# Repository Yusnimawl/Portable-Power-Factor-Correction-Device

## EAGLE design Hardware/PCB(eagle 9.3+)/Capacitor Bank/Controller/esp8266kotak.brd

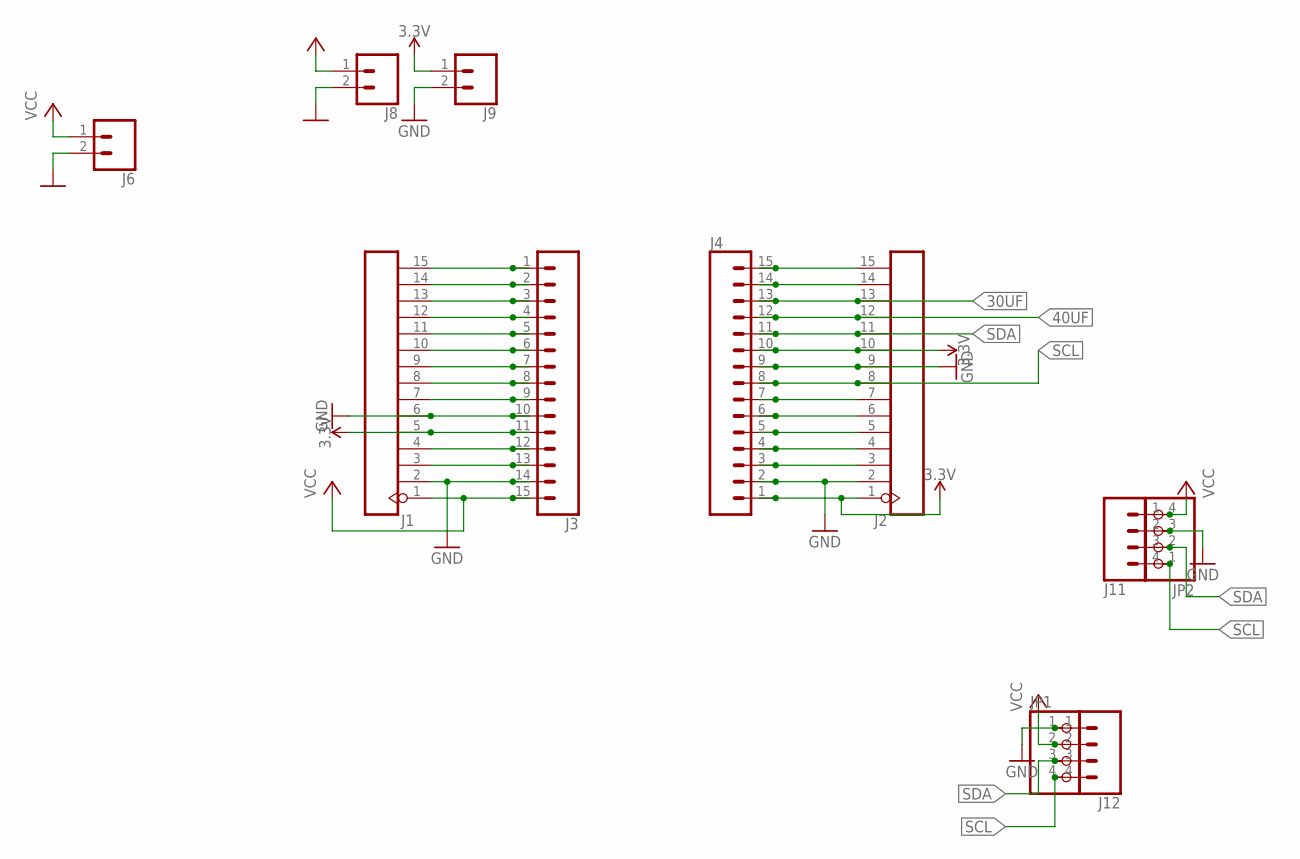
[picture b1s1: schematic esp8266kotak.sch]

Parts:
J1, J2: HEADER-15P2.54; 15P-2.54
J3, J4: CONN_15; 1X15
J6, J8, J9: CONN_02; 1X02
J11, J12: CONN_04; 1X04
JP1, JP2: PINHD-1X4/90; 1X04/90

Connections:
3.3V: J1.5, J2.1, J2.10, J3.11, J4.1, J4.10, J9.1
30UF: J2.13, J4.13
40UF: J2.12, J4.12
GND: J1.2, J1.6, J2.2, J2.9, J3.10, J3.14, J4.2, J4.9, J6.2, J8.2, J9.2, J11.2, J12.1, JP1.1, JP2.3
unnamed: J1.3, J3.13
unnamed: J1.4, J3.12
unnamed: J1.7, J3.9
unnamed: J1.8, J3.8
unnamed: J1.9, J3.7
unnamed: J1.10, J3.6
unnamed: J1.11, J3.5
unnamed: J1.12, J3.4
unnamed: J1.13, J3.3
unnamed: J1.14, J3.2
unnamed: J1.15, J3.1
unnamed: J2.3, J4.3
unnamed: J2.4, J4.4
unnamed: J2.5, J4.5
unnamed: J2.6, J4.6
unnamed: J2.7, J4.7
unnamed: J2.14, J4.14
unnamed: J2.15, J4.15
SCL: J2.8, J4.8, J11.4, J12.4, JP1.4, JP2.1
SDA: J2.11, J4.11, J11.3, J12.3, JP1.3, JP2.2
VCC: J1.1, J3.15, J6.1, J8.1, J11.1, J12.2, JP1.2, JP2.4

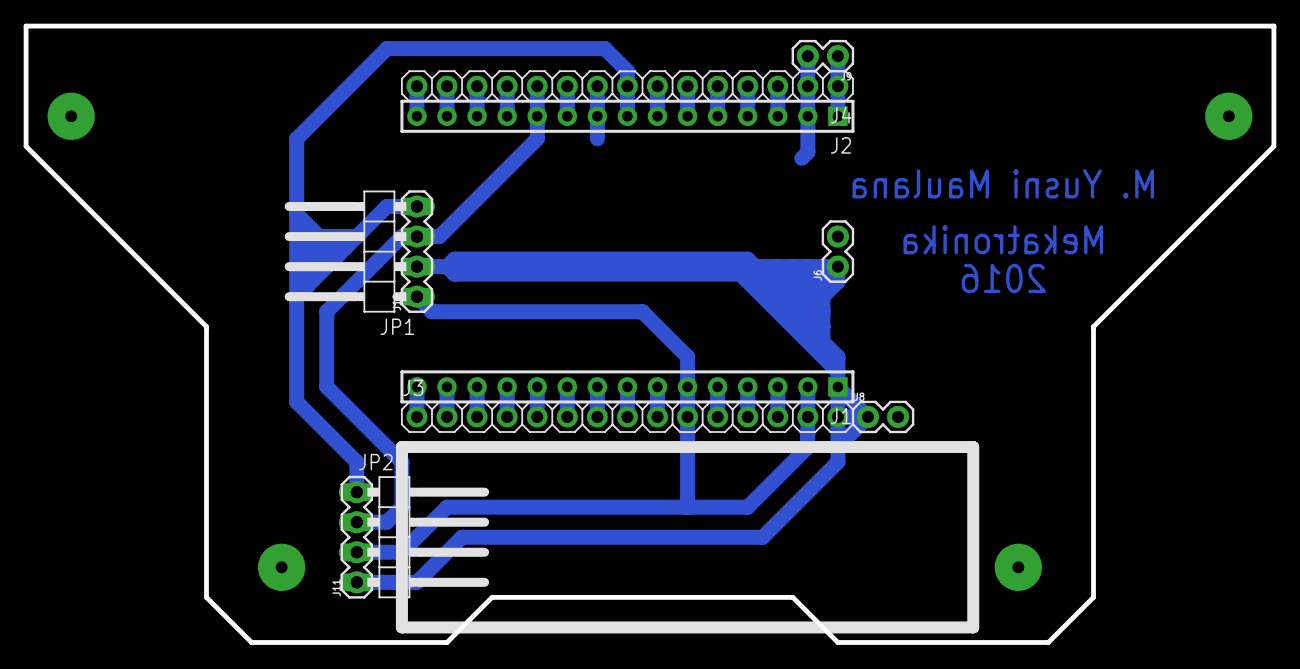
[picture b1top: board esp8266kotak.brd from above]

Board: 2 copper layers, 105.4 x 52.1 mm, 11 parts (0 on the bottom side), 25 nets.

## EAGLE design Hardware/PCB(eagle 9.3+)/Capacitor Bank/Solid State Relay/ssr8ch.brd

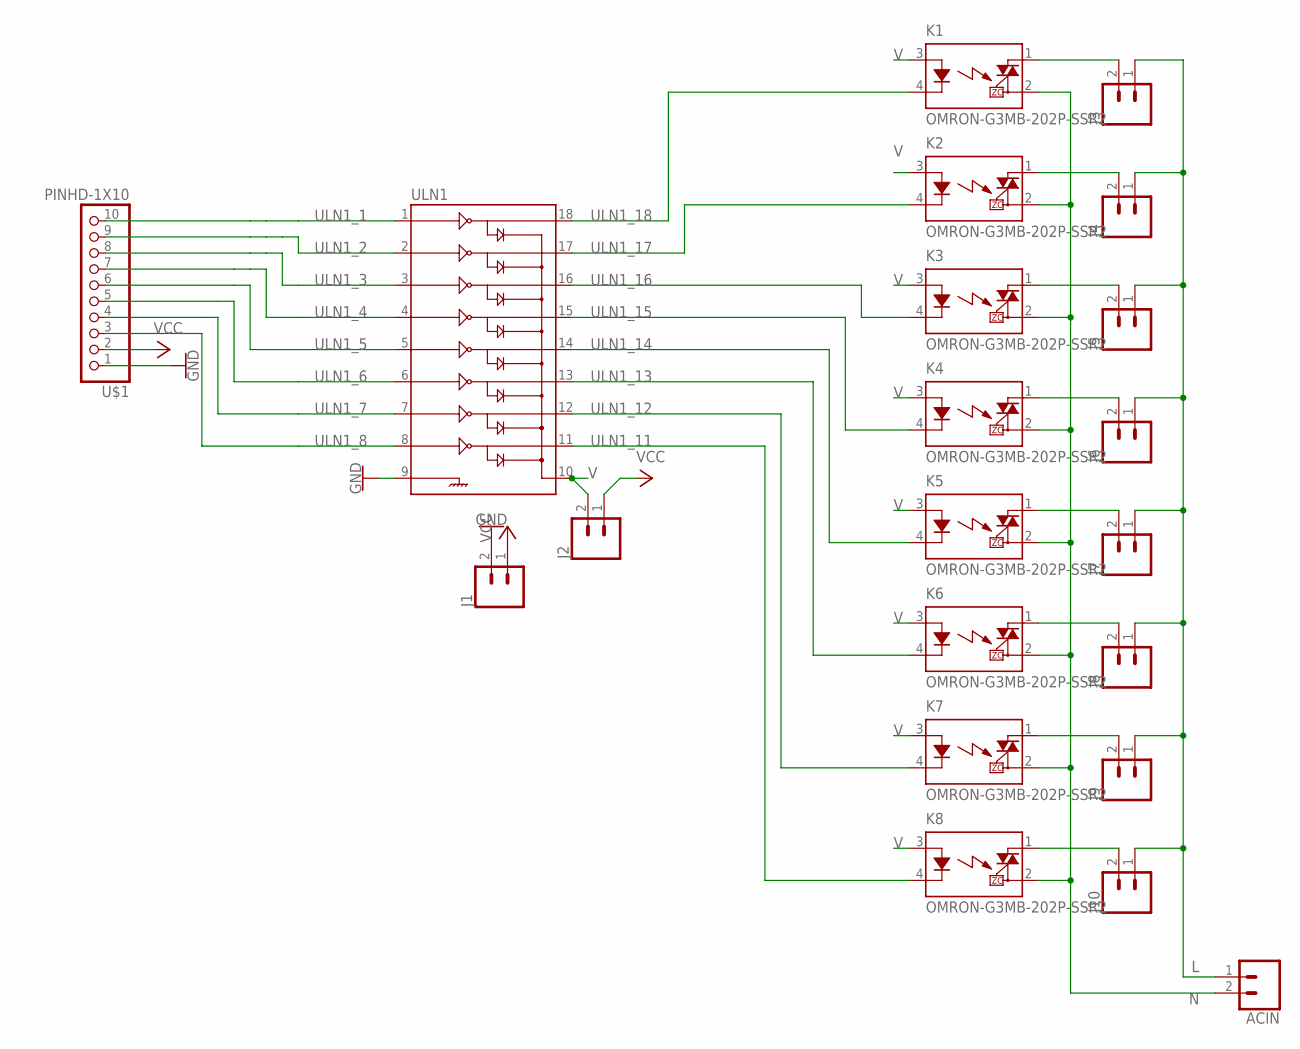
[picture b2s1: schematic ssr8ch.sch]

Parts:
ACIN: CONN_025MM; SCREWTERMINAL-5MM-2
J1, J3, J4, J5, J6, J7, J8, J9, J10: CONN_025MM; SCREWTERMINAL-5MM-2
J2: CONN_021X02_NO_SILK; 1X02_NO_SILK
K1, K2, K3, K4, K5, K6, K7, K8: OMRON-G3MB-202P-SSR2; OMRON-G3MB-202P-SSR
U$1: PINHD-1X10; 1X10-BIG
ULN1: ULN2803DIP; DIL18

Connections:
GND: J1.2, U$1.1, ULN1.9
L: ACIN.1, J3.1, J4.1, J5.1, J6.1, J7.1, J8.1, J9.1, J10.1
N: ACIN.2, K1.2 (DS2), K2.2 (DS2), K3.2 (DS2), K4.2 (DS2), K5.2 (DS2), K6.2 (DS2), K7.2 (DS2), K8.2 (DS2)
unnamed: J3.2, K1.1 (DS1)
unnamed: J5.2, K3.1 (DS1)
unnamed: J6.2, K4.1 (DS1)
unnamed: J7.2, K5.1 (DS1)
unnamed: J8.2, K6.1 (DS1)
unnamed: J9.2, K7.1 (DS1)
unnamed: J10.2, K8.1 (DS1)
unnamed: J4.2, K2.1 (DS1)
ULN1_1: U$1.10, ULN1.1
ULN1_2: U$1.9, ULN1.2
ULN1_3: U$1.8, ULN1.3
ULN1_4: U$1.7, ULN1.4
ULN1_5: U$1.6, ULN1.5
ULN1_6: U$1.5, ULN1.6
ULN1_7: U$1.4, ULN1.7
ULN1_8: U$1.3, ULN1.8
ULN1_11: K8.4 (K), ULN1.11
ULN1_12: K7.4 (K), ULN1.12
ULN1_13: K6.4 (K), ULN1.13
ULN1_14: K5.4 (K), ULN1.14
ULN1_15: K4.4 (K), ULN1.15
ULN1_16: K3.4 (K), ULN1.16
ULN1_17: K2.4 (K), ULN1.17
ULN1_18: K1.4 (K), ULN1.18
V: J2.2, K1.3 (A), K2.3 (A), K3.3 (A), K4.3 (A), K5.3 (A), K6.3 (A), K7.3 (A), K8.3 (A), ULN1.10
VCC: J1.1, J2.1, U$1.2

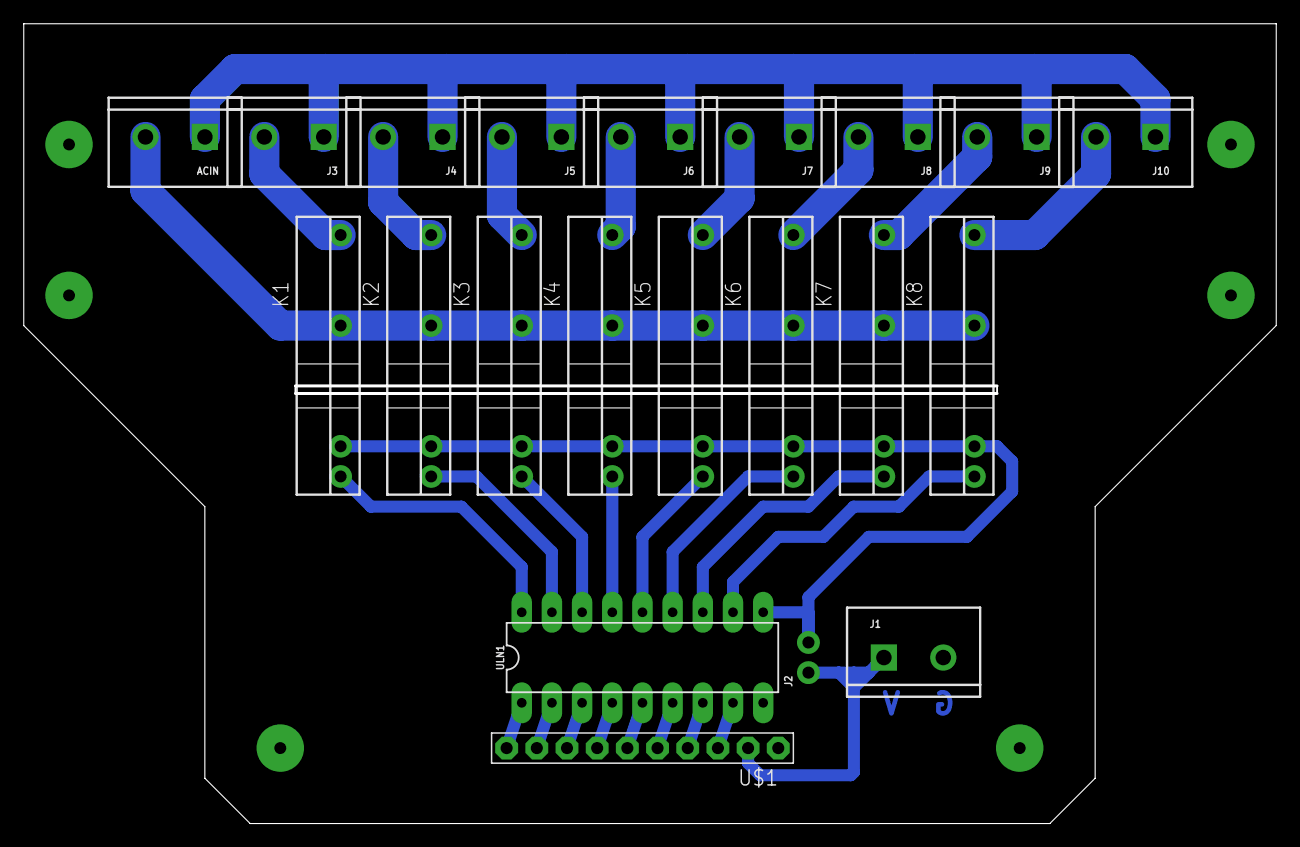
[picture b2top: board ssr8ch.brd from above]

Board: 2 copper layers, 105.2 x 67.1 mm, 21 parts (0 on the bottom side), 29 nets.

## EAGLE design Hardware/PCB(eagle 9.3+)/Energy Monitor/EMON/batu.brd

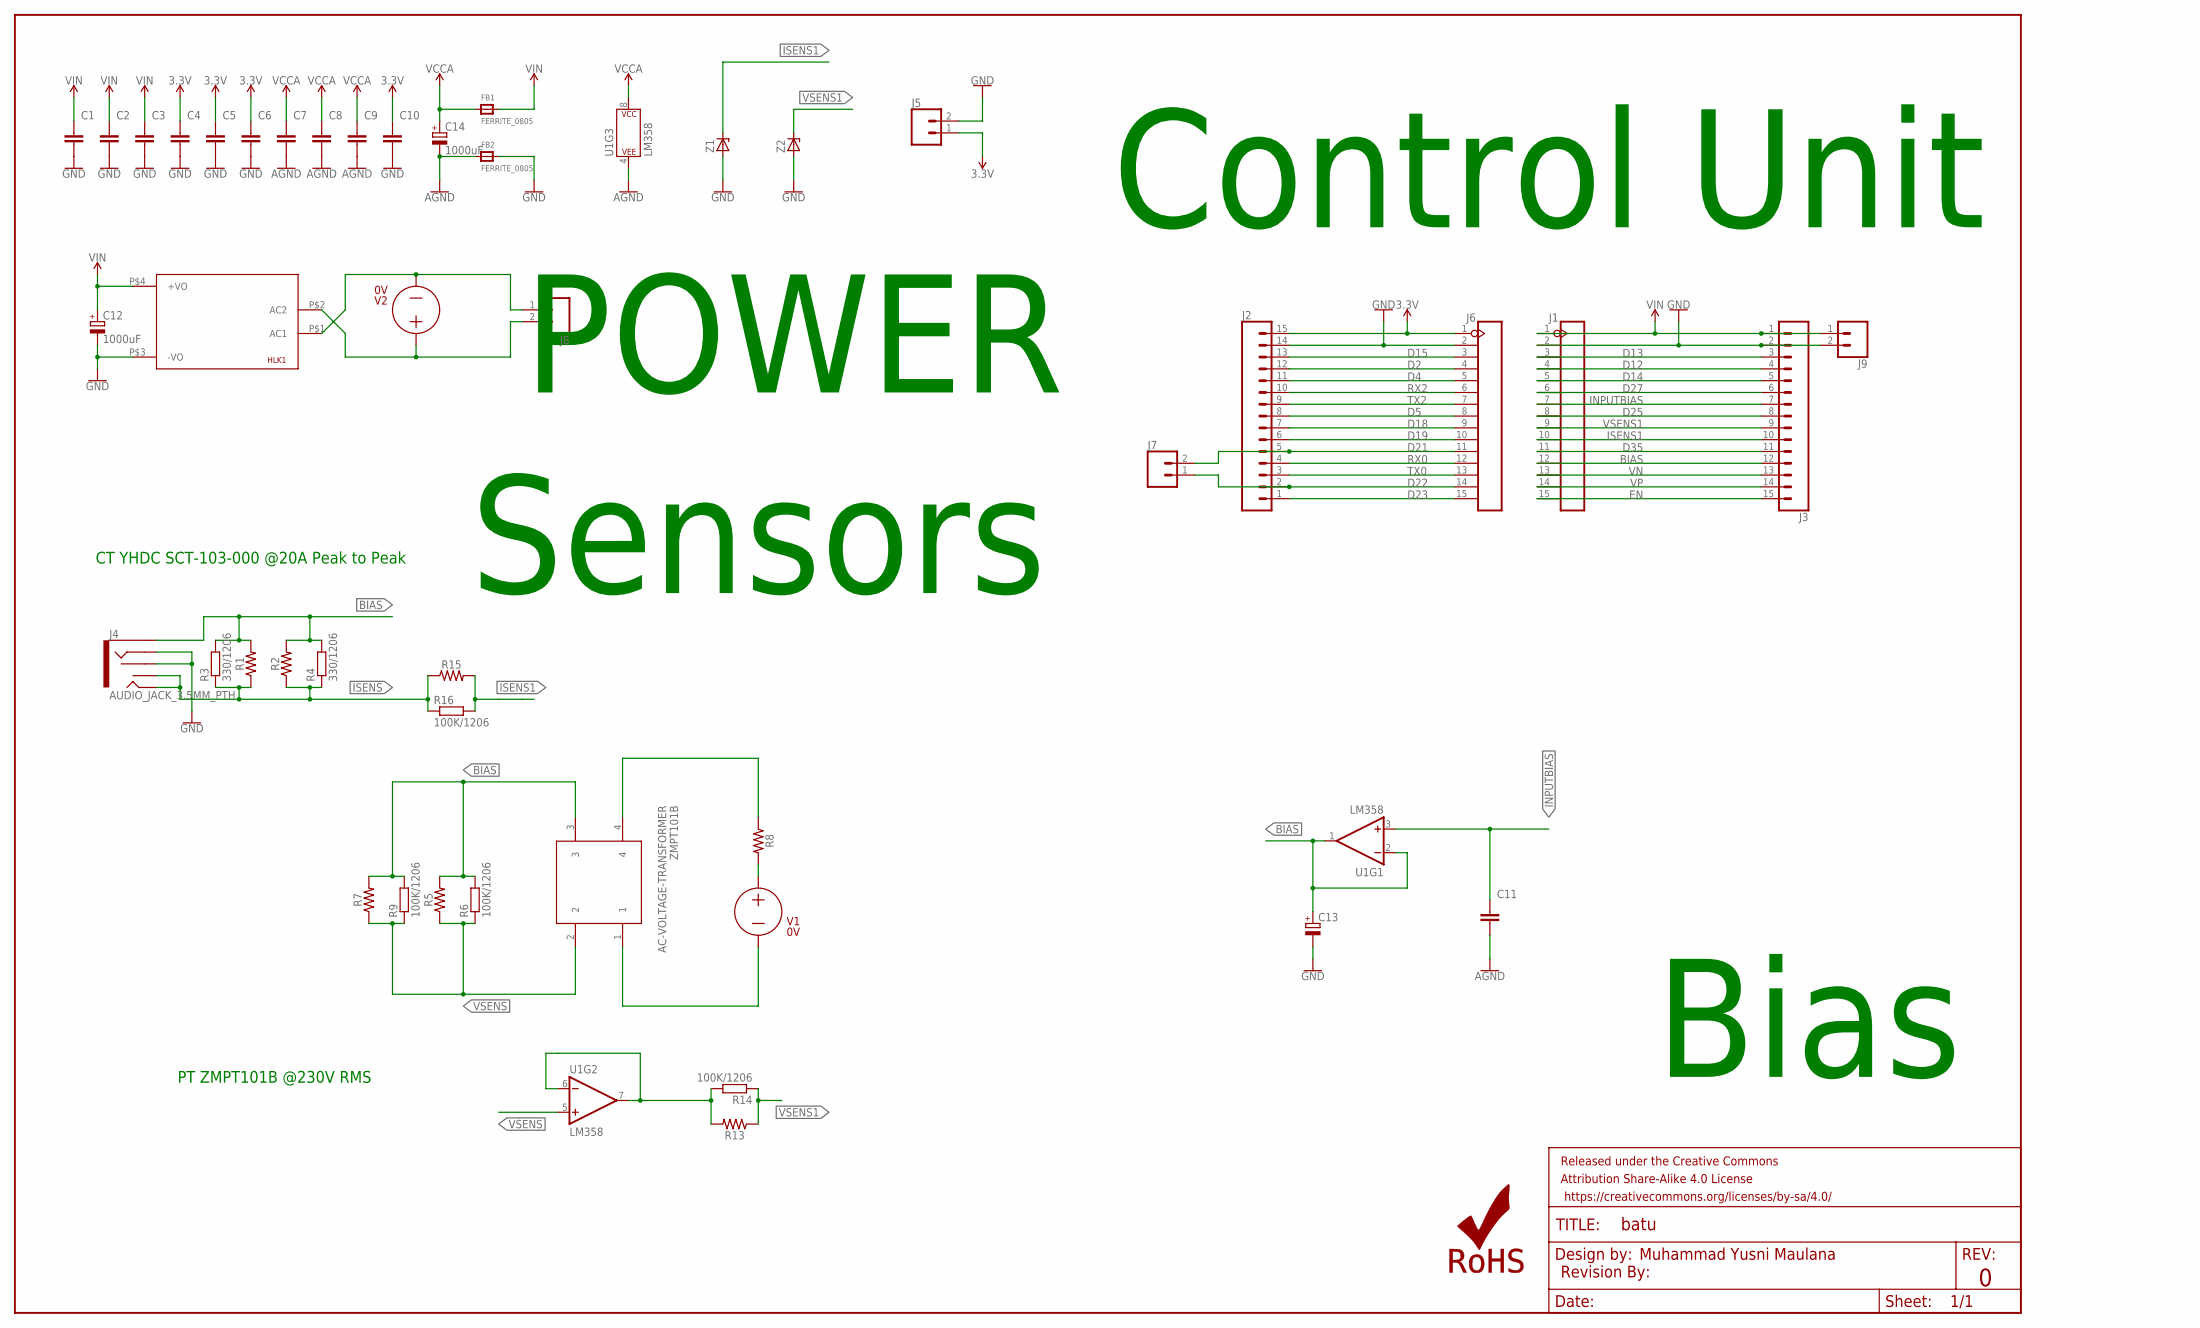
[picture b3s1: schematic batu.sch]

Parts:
C1, C3, C4, C6, C7, C10: 0.1uF; C1206
C2, C5, C8, C9, C11: 10uF; C1206
C12, C14: 1000uF; SANYO-OSCON_C6
C13: CPOL-EUSANYO_C6; SANYO-OSCON_C6
FB1, FB2: FERRITE_0805; _0805
FRAME1: FRAME-LEDGER; CREATIVE_COMMONS
HLK1: HLK-PM013W; HLK-PM01
J1, J6: HEADER-15P2.54; 15P-2.54
J2, J3: CONN_15; 1X15
J4: AUDIO_JACK_3.5MM_PTH; AUDIO-JACK
J5, J7, J9: CONN_021X02_NO_SILK; 1X02_NO_SILK
J8: CONN_025MM; SCREWTERMINAL-5MM-2
LOGO3: REVISION
LOGO8: ROHS_LOGO; ROHS_LOGO_0.18_IN
R1, R2, R5, R7, R8, R13, R15: AXIAL-0.3
R3, R4: 330/1206; R1206
R6, R9, R14, R16: 100K/1206; R1206
U1: LM358; DIL08
Z1, Z2: ZENER-DIODESOD80C; SOD80C
ZMPT101B: AC-VOLTAGE-TRANSFORMER; AC-VOLTAGE-SENSOR

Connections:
3.3V: C4.1, C5.1, C6.1, C10.1, J2.15, J5.1, J6.1
AGND: C7.2, C8.2, C9.2, C11.2, C14.-, FB2.1, U1.4 (P$V-)
BIAS: C13.+, J1.12, J3.12, J4.SLEEVE, R1.P$2 (2), R2.P$2 (2), R3.2, R4.2, R5.P$2 (2), R6.2, R7.P$2 (2), R9.2, U1.1 (OUT), U1.2 (-IN), ZMPT101B.3
D2: J2.12, J6.4
D4: J2.11, J6.5
D5: J2.8, J6.8
D12: J1.4, J3.4
D13: J1.3, J3.3
D14: J1.5, J3.5
D15: J2.13, J6.3
D18: J2.7, J6.9
D19: J2.6, J6.10
D21: J2.5, J6.11, J7.2
D22: J2.2, J6.14, J7.1
D23: J2.1, J6.15
D25: J1.8, J3.8
D27: J1.6, J3.6
D35: J1.11, J3.11
EN: J1.15, J3.15
GND: C1.2, C2.2, C3.2, C4.2, C5.2, C6.2, C10.2, C12.-, C13.-, FB2.2, HLK1.P$3 (-VO), J1.2, J2.14, J3.2, J4.RING, J4.RSH, J5.2, J6.2, J9.2, Z1.A, Z2.A
INPUTBIAS: C11.1, J1.7, J3.7, U1.3 (+IN)
ISENS: J4.TIP, J4.TSH, R1.P$1 (1), R2.P$1 (1), R3.1, R4.1, R15.P$1 (1), R16.1
ISENS1: J1.10, J3.10, R15.P$2 (2), R16.2, Z1.C
L: HLK1.P$2 (AC2), J8.2, R8.P$2 (2)
N: HLK1.P$1 (AC1), J8.1, ZMPT101B.1
unnamed: R8.P$1 (1), ZMPT101B.4
RX0: J2.4, J6.12
RX2: J2.10, J6.6
TX0: J2.3, J6.13
TX2: J2.9, J6.7
VCCA: C7.1, C8.1, C9.1, C14.+, FB1.1, U1.8 (P$V+)
VIN: C1.1, C2.1, C3.1, C12.+, FB1.2, HLK1.P$4 (+VO), J1.1, J3.1, J9.1
VN: J1.13, J3.13
VP: J1.14, J3.14
VSENS: R5.P$1 (1), R6.1, R7.P$1 (1), R9.1, U1.5 (+IN), ZMPT101B.2
VSENS1: J1.9, J3.9, R13.P$1 (1), R14.1, Z2.C
VSENS2: R13.P$2 (2), R14.2, U1.6 (-IN), U1.7 (OUT)

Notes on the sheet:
Muhammad Yusni Maulana
POWER
Control Unit
Bias
Sensors
CT YHDC SCT-103-000 @20A Peak to Peak
PT ZMPT101B @230V RMS

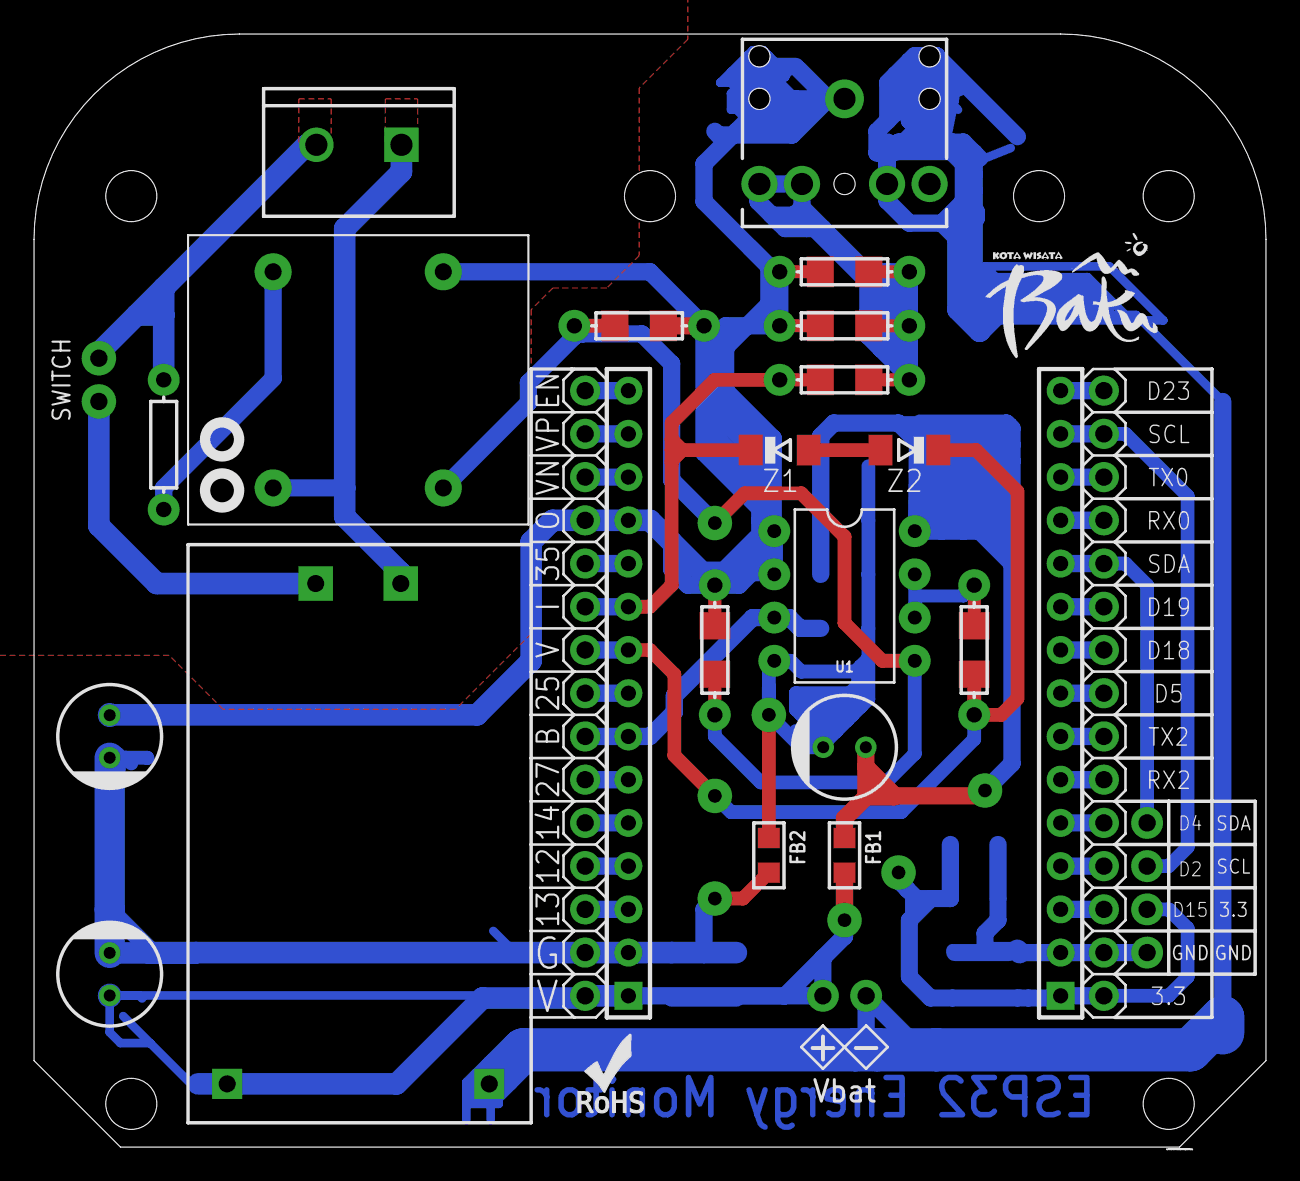
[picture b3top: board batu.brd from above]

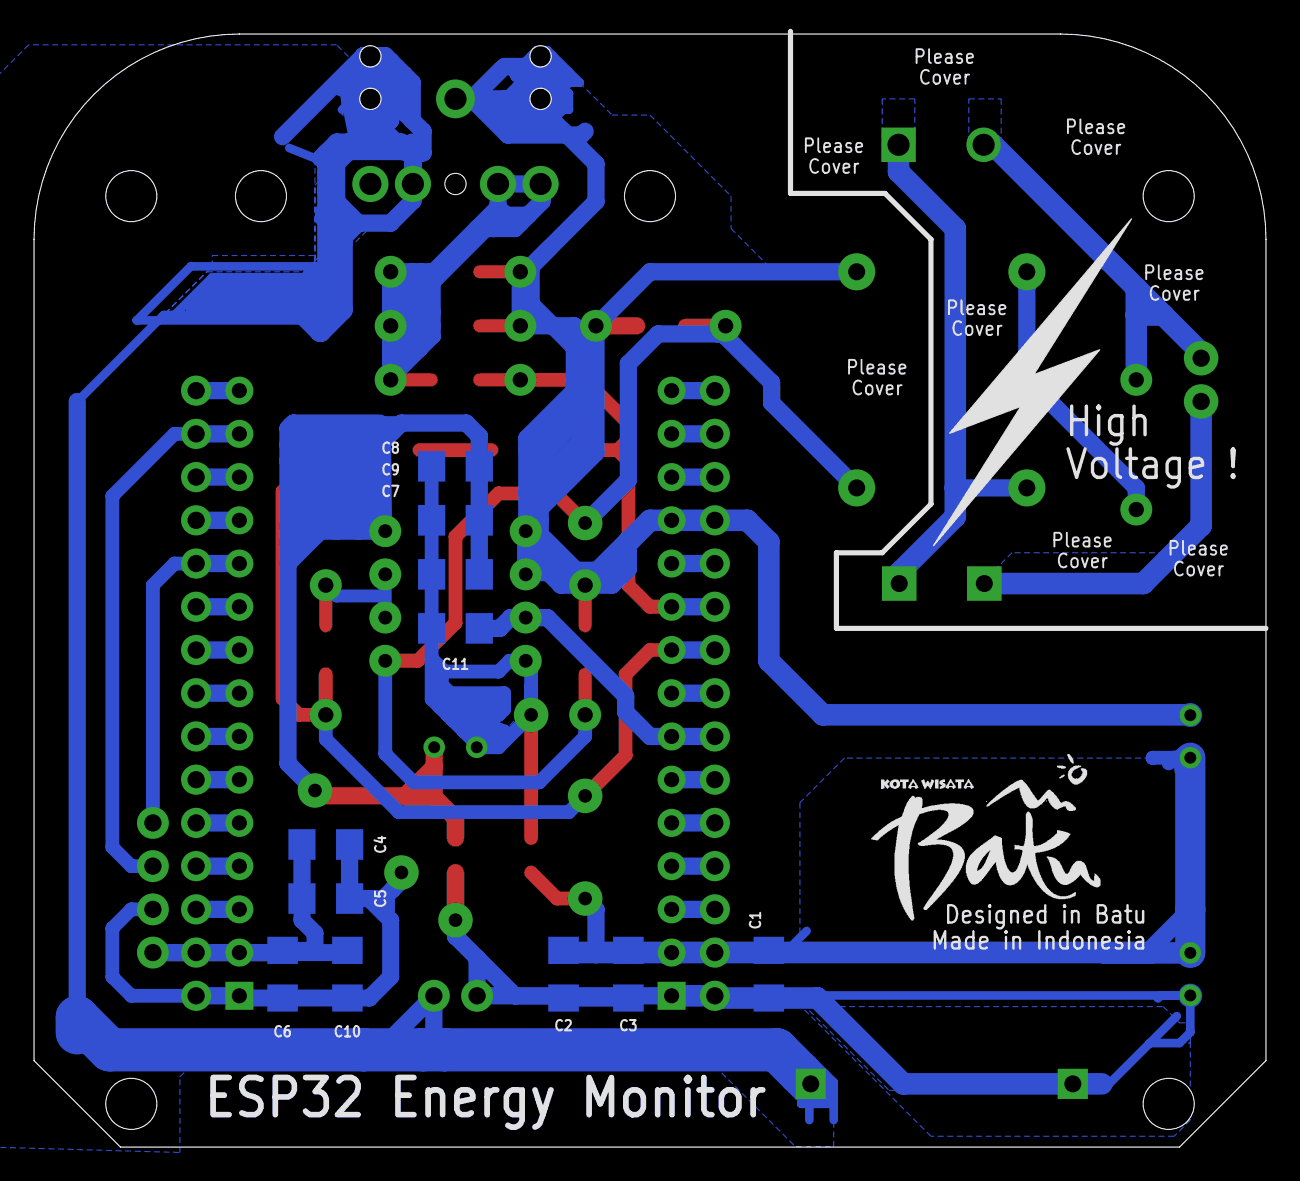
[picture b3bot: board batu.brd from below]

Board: 2 copper layers, 72.4 x 65.4 mm, 46 parts (11 on the bottom side), 37 nets.

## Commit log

2022-05-29 added files

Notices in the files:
parts and their libraries:
SparkFun-Connectors: Licensing: Creative Commons ShareAlike 4.0 International - https://creativecommons.org/licenses/by-sa/4.0
for the universe: Released under the Creative Commons Attribution Share-Alike 4.0 License
for the universe: https://creativecommons.org/licenses/by-sa/4.0
